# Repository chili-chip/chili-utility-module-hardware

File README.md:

# chili-utility-module

KiCad 10 project for the **chilichip utility module**: a small add-on board for the [chilichip console](https://github.com/chili-chip/vgc-zero-hardware) with a gyroscope/accelerometer, a vibration motor and a real-time clock. Everything sits on one I²C bus, so the module needs only the console's three free GPIOs. The RTC is backed by the console's LiPo through its VSYS rail.

Status: **v2.0.0, schematic and PCB done.** The board is routed, DRC is clean (0 violations, 0 unconnected, matches the schematic), and ERC is clean.

v2.0.0 shrinks the board from 30 × 32 mm to 16.4 × 14.8 mm so it fits on the back of the console (with the RP2350-Plus and its LiPo) between the MCU, the battery and a display mounting hole:
- the CR1220 coin cell is gone: the RTC's backup input comes from the console's VSYS on a sixth castellation (VBAT);
- the 10 mm coin motor with wire leads is replaced by a reflow-solderable 4.3 mm SMD ERM (Vybronics VZ43FC1B5640007L).

| Top | Bottom |
|:---:|:---:|
|  |  |

## Parts

| Ref | Function | Part | LCSC |
|-----|----------|------|------|
| U1 | Gyro + accelerometer | **ST LSM6DS3TR-C**, 6-axis IMU, LGA-14 2.5 × 3 mm | [C967633](https://www.lcsc.com/product-detail/C967633.html) |
| U2 | Real-time clock | **Micro Crystal RV-3028-C7**, crystal built in, 45 nA, SON-8 1.5 × 3.2 mm | [C3019759](https://www.lcsc.com/product-detail/C3019759.html) |
| U3 | Haptic driver | **TI DRV2605L**, I²C ERM/LRA driver with 123 built-in effects, VSSOP-10 | [C527464](https://www.lcsc.com/product-detail/C527464.html) |
| M1 | Vibration motor | **Vybronics VZ43FC1B5640007L**, SMD cylindrical ERM, 4.3 × 4.5 × 12 mm, 3 V, 77 mA typ, reflow-solderable | not on LCSC: [Digi-Key 12323649](https://www.digikey.com/en/products/detail/vybronics-inc/VZ43FC1B5640007L/12323649) |
| C1–C4, C6 | Decoupling | 100 nF 0402, Samsung CL05B104KO5NNNC | C1525 |
| C5, C7 | Driver VDD / REG | 1 µF 0402, Samsung CL05A105KA5NQNC | C52923 |
| R1, R2 | I²C pull-ups | 4.7 kΩ 0402, UNI-ROYAL 0402WGF4701TCE | C25900 |
| R3, R4 | INT pull-up, EVI tie-down | 10 kΩ 0402, UNI-ROYAL 0402WGF1002TCE | C25744 |

Why these parts:
- **LSM6DS3TR-C:** active ST part at about $0.60–0.90, with mature drivers (ST's platform-independent C driver, Adafruit, NuttX).
- **RV-3028-C7:** no external crystal or load capacitors, ±1 ppm, and an automatic switchover to the backup supply (rated 1.1–5.5 V, so the console's VSYS at 3.4–4.95 V can feed it directly; about 115 nA in backup).
- **DRV2605L:** plays haptic effects over I²C, so the motor needs no PWM pin or MOSFET. That matters because the console has no GPIO left for one.

Alternatives considered:
- **QST QMI8658A** IMU: fewer drivers and no KiCad symbol.
- **NXP PCF85063A** RTC: needs an external crystal and draws about 5× more current.
- **MOSFET + flyback diode** for the motor: needs a spare PWM GPIO.
- **CR1220 coin cell** (v1): takes a 20 × 13 mm holder. The console's LiPo holds the RTC for years at 115 nA, as long as the console's off state cuts everything else.

## Connector J1 (to the console)

| Pin | Signal | Console | Notes |
|-----|--------|---------|-------|
| 1 | 3V3 | RP2350-Plus 3V3 | |
| 2 | SDA | GP0 (I2C0 SDA) | 4.7 kΩ pull-up R1 on the module |
| 3 | SCL | GP1 (I2C0 SCL) | 4.7 kΩ pull-up R2 on the module |
| 4 | INT | GP2 | open-drain, shared by IMU INT1 and RTC ~INT; 10 kΩ pull-up R3 |
| 5 | GND | GND | |
| 6 | VBAT | VSYS (pin 39) | RTC backup supply: always on while the console's LiPo is fitted, 3.4–4.95 V. 100 nF C4 at the RTC |

I²C addresses: IMU **0x6A** (SA0 to GND), RTC **0x52**, haptic driver **0x5A**.

GP0/GP1 are also the RP2350's default UART0 pins, so with this module fitted, use USB serial for debug output.

## Firmware setup the hardware relies on

- **IMU:** set INT1 to open-drain (`CTRL3_C` bit `PP_OD = 1`) before enabling any interrupt, because it shares the INT line with the RTC.
- **RTC:**
  - Enable backup switchover in level-switching mode (`BSM = 11` in register 37h) and store it to EEPROM. Switchover is disabled when the chip ships.
  - Leave the trickle charger off (`TCE = 0`, the default): VBACKUP is fed from the console's VSYS, never charged from VDD.
  - CLKOUT outputs 32.768 kHz by default; turn it off to save current.
- **Haptic driver:** select ERM mode and the ERM effect library, then run auto-calibration once for the motor (rated 3.0 V, 2.5–3.4 V operating). The motor's leads are swapped (OUT+ to its − pad) to keep the traces apart; an ERM vibrates the same in either direction. EN is tied high, so put the driver in standby through the `MODE` register when idle.

## ERC

ERC is clean. The project's `LSM6DS3TR-C` symbol has four pin types adjusted from KiCad's original, all matching how this design uses them:
- INT1/INT2 are open-collector, because firmware always sets them to open-drain so they can share the INT line with the RTC.
- SDO/SA0 and SDx are passive, because they're tied to GND: SA0 as an address strap, SDx as the unused auxiliary I²C master.

## Still to check

- **IMU SDx/SCx tie-off:** I tied them to GND, which is what secondary pin summaries say ("connect to VDDIO or GND" when unused). Check this against ST's LSM6DS3TR-C datasheet (DocID030071) pin table.
- **Power budget:** the motor draws about 77 mA (100 mA max) at 3 V while running, from the RP2350-Plus's 3.3 V output.
- **Motor sourcing:** the VZ43FC1B isn't stocked by LCSC. For JLCPCB assembly, use their global sourcing (Digi-Key) or consign the parts, or pick an LCSC-stocked SMD ERM with the same land pattern.

## Footprints

| Ref | Footprint | Source |
|-----|-----------|--------|
| J1 | `Castellated_1x06_P2.54mm` | Same castellated pads as the audio and buttons modules: 1.0 mm drill, 2.4 × 1.6 mm, on the board edge |
| M1 | `Motor_ERM_SMD_Vybronics_VZ43FC1B` | Vybronics datasheet land pattern: frame pad 3.4 × 9 mm (no net), terminals 1.3 × 1.4 mm. The counterweight end overhangs the frame pad and must stay clear |
| U2 | `MicroCrystal_C7_SON-8_1.5x3.2mm_P0.9mm` | Copy of KiCad's footprint, because KiCad 10 doesn't ship the 3D model it references |
| U1, U3, passives | KiCad standard library | |

**3D models:** U1, U3 and the passives use KiCad's library models. U2 uses LCSC's STEP model (from their EasyEDA library) and M1 Vybronics' STEP model, stored in `3d-models/`.

## PCB

- **Board:** 16.4 × 14.8 mm, 2 layers, all parts on the top side, 4.3 mm tall at the motor. The bottom sits flat on the back of the console once J1's castellations are soldered; the console's `UtilityModule` footprint has the matching lands.
- **Placement:**
  - J1 on the left edge, with the I²C/INT pull-ups in a column next to their castellations.
  - RTC at the top (next to VBAT), IMU below it, haptic driver at the bottom, each with its capacitors to its right.
  - Motor along the right edge, terminals at the bottom next to the driver's outputs.
- **Ground:** GND pour on both layers. SMD pads connect solid, through-hole pads through thermal spokes, and J1's GND castellation solid.
- **Routing:** autorouted with Freerouting, GND included as tracks, with keep-outs along the edges and between the castellations for the 0.5 mm copper-to-edge clearance. Tracks are 0.15 mm, necked to 0.125 mm where they pass fine-pitch pads, with 0.15 mm clearance; JLCPCB's minimum is 0.127 mm (DRC minimum set to 0.12 mm).
- **Silkscreen:** the version on top; J1 pin labels (VB, G, IN, SC, SD, 3V) and the module name on the bottom, since the top has no room. Reference designators are on the fab layer.

## Ordering from JLCPCB

Every tagged release has `chili-utility-module-<version>-gerbers.zip`, `-bom.csv` and `-cpl.csv` attached. Run `scripts/export-jlcpcb.sh` to build them locally into `production/`.

1. Upload the gerber zip on [jlcpcb.com](https://jlcpcb.com/) and select **2 layers, 1.6 mm, Castellated Holes: Yes**.
2. Turn on **PCB Assembly** (top side) and upload the BOM and CPL.
3. In the placement preview, check pin 1 of U1–U3 and the motor's orientation (terminals at the bottom, next to U3).
4. The motor (M1) has no LCSC part number: source it through JLCPCB global sourcing or consign it. Don't wash the board after assembly: the motor must not get flux washes or conformal coating.

CI runs ERC, DRC and the export on every push and pull request. A `v*` tag publishes a release with the files attached.

## Files

| Path | Contents |
|------|----------|
| `chili-utility-module.kicad_sch` | Schematic |
| `chili-utility-module.kicad_sym`, `sym-lib-table` | Project symbols: LSM6DS3TR-C, RV-3028-C7, DRV2605L, Motor_ERM. Copied from KiCad 10's library, with manufacturer, part number and LCSC fields added |
| `chili-utility-module.pretty/`, `fp-lib-table` | Project footprints: J1 castellated 1×06, M1 Vybronics SMD motor, U2 SON-8 |
| `3d-models/` | STEP models for M1 and U2 |
| `chili-utility-module.kicad_pcb` | PCB |
| `scripts/export-jlcpcb.sh` | Builds the JLCPCB gerber zip, BOM and CPL |
| `scripts/render-images.sh` | Regenerates the renders in `docs/images/` |
| `.github/workflows/main.yml` | CI and release workflow |

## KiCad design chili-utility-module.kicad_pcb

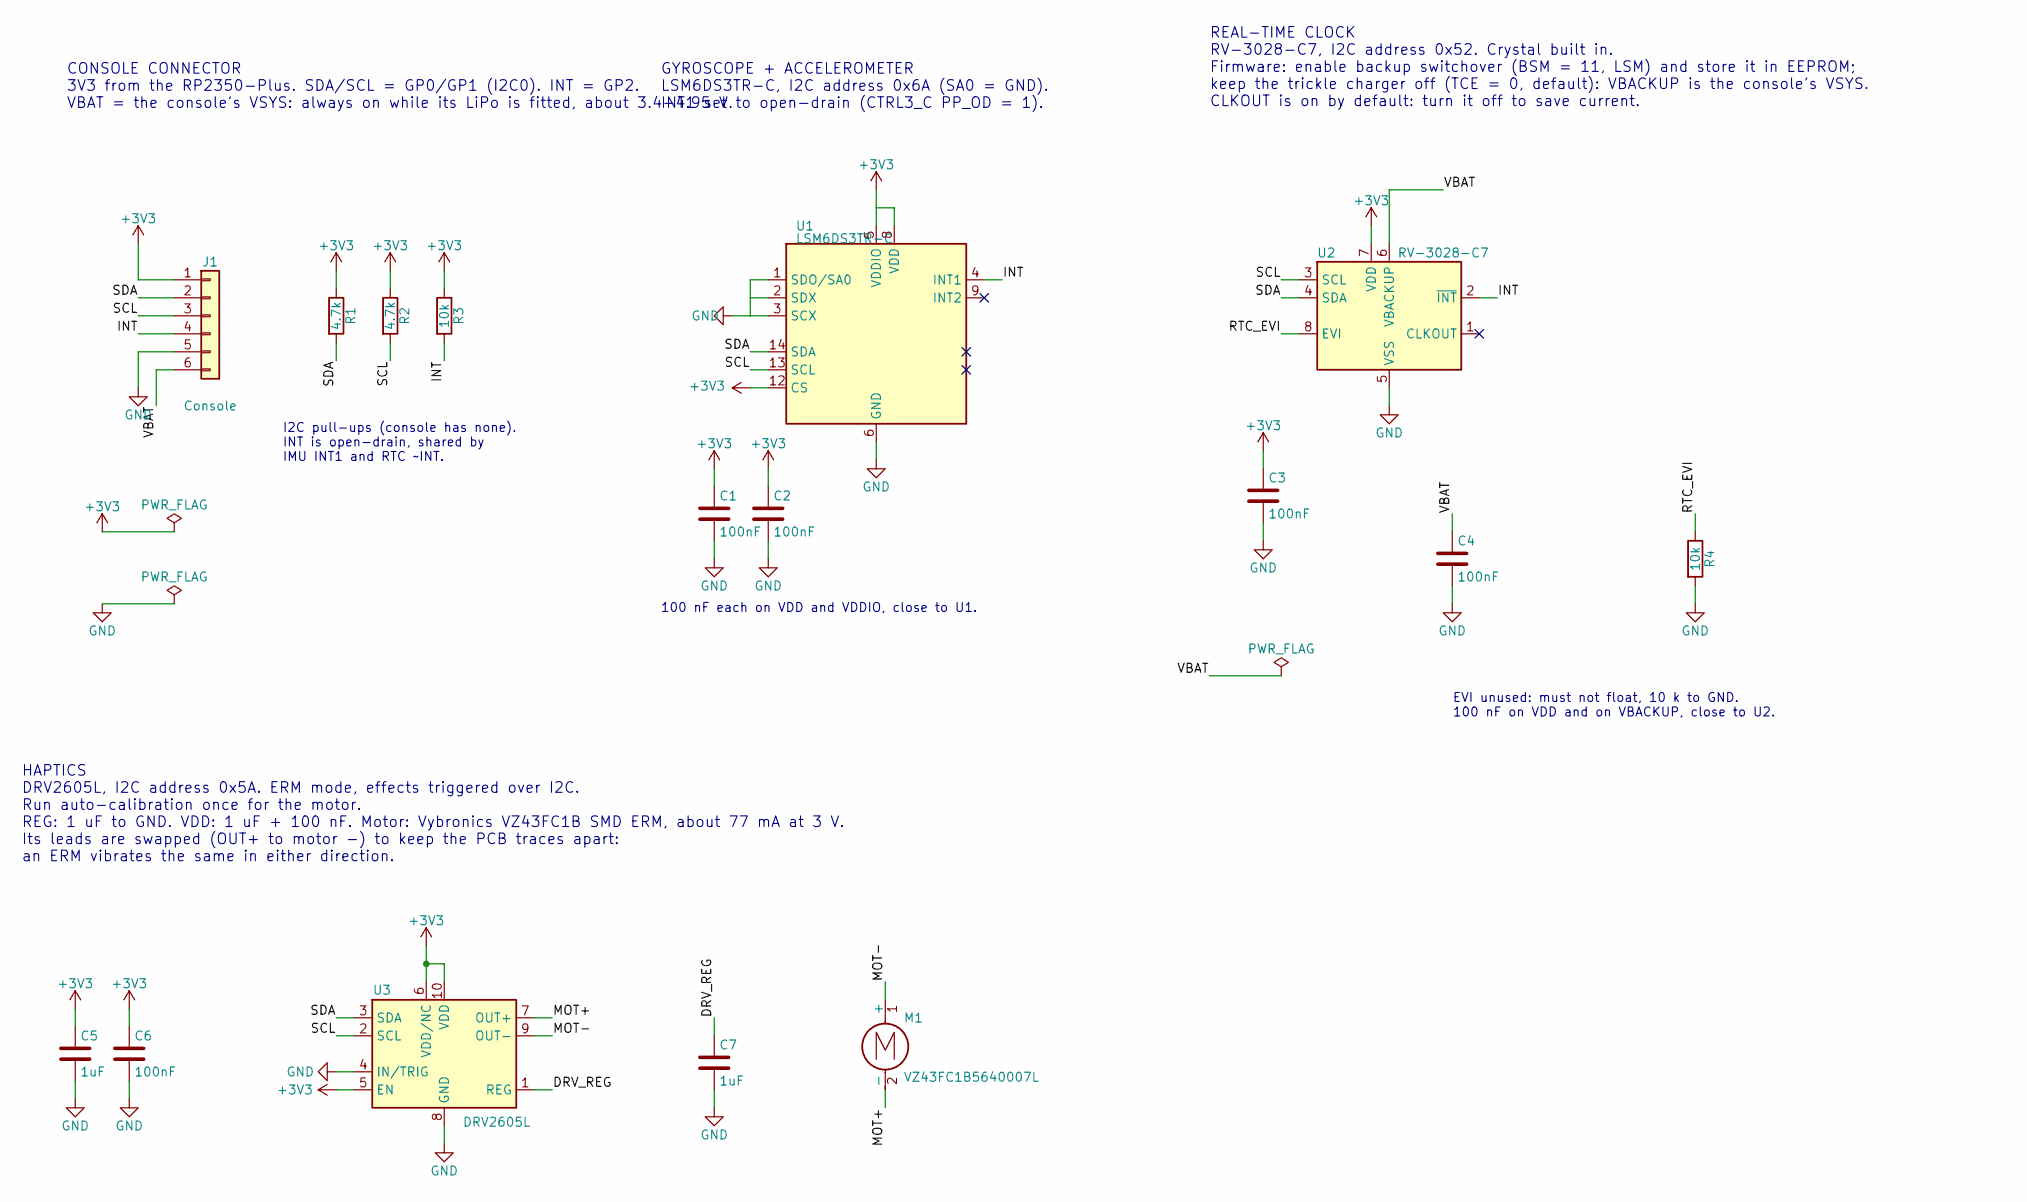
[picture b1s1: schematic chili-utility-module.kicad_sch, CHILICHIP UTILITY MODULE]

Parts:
C1, C2, C3, C4, C6: 100nF; C_0402_1005Metric; MPN CL05B104KO5NNNC; LCSC C1525
C5, C7: 1uF; C_0402_1005Metric; MPN CL05A105KA5NQNC; LCSC C52923
J1: Console; Castellated_1x06_P2.54mm
M1: VZ43FC1B5640007L; Motor_ERM_SMD_Vybronics_VZ43FC1B; MPN VZ43FC1B5640007L
R1, R2: 4.7k; R_0402_1005Metric; MPN 0402WGF4701TCE; LCSC C25900
R3, R4: 10k; R_0402_1005Metric; MPN 0402WGF1002TCE; LCSC C25744
U1: LSM6DS3TR-C; LGA-14_3x2.5mm_P0.5mm_LayoutBorder3x4y; MPN LSM6DS3TR-C; LCSC C967633
U2: RV-3028-C7; MicroCrystal_C7_SON-8_1.5x3.2mm_P0.9mm; MPN RV-3028-C7-32.768kHz-1ppm-TA-QC; LCSC C3019759
U3: DRV2605L; TSSOP-10_3x3mm_P0.5mm; MPN DRV2605LDGSR; LCSC C527464

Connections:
+3V3: C1.1, C2.1, C3.1, C5.1, C6.1, J1.1, R1.1, R2.1, R3.1, U1.5 (VDDIO), U1.8 (VDD), U1.12 (CS), U2.7 (VDD), U3.5 (EN), U3.6 (VDD/NC), U3.10 (VDD)
/DRV_REG: C7.1, U3.1 (REG)
/INT: J1.4, R3.2, U1.4 (INT1), U2.2 (~INT)
/MOT+: M1.2 (-), U3.7 (OUT+)
/MOT-: M1.1 (+), U3.9 (OUT-)
/RTC_EVI: R4.1, U2.8 (EVI)
/SCL: J1.3, R2.2, U1.13 (SCL), U2.3 (SCL), U3.2 (SCL)
/SDA: J1.2, R1.2, U1.14 (SDA), U2.4 (SDA), U3.3 (SDA)
/VBAT: C4.1, J1.6, U2.6 (VBACKUP)
GND: C1.2, C2.2, C3.2, C4.2, C5.2, C6.2, C7.2, J1.5, R4.2, U1.1 (SDO/SA0), U1.2 (SDX), U1.3 (SCX), U1.6 (GND), U1.7 (GND), U2.5 (VSS), U3.4 (IN/TRIG), U3.8 (GND)

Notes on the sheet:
100 nF each on VDD and VDDIO, close to U1.
CONSOLE CONNECTOR 3V3 from the RP2350-Plus. SDA/SCL = GP0/GP1 (I2C0). INT = GP2. VBAT = the console's VSYS: always on while its LiPo is fitted, about 3.4-4.95 V.
I2C pull-ups (console has none). INT is open-drain, shared by IMU INT1 and RTC ~INT.
HAPTICS DRV2605L, I2C address 0x5A. ERM mode, effects triggered over I2C. Run auto-calibration once for the motor. REG: 1 uF to GND. VDD: 1 uF + 100 nF. Motor: Vybronics VZ43FC1B SMD ERM, about 77 mA at 3 V. Its leads are swapped (OUT+ to motor -) to keep the PCB traces apart: an ERM vibrates the s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
GYROSCOPE + ACCELEROMETER LSM6DS3TR-C, I2C address 0x6A (SA0 = GND). INT1 set to open-drain (CTRL3_C PP_OD = 1).
REAL-TIME CLOCK RV-3028-C7, I2C address 0x52. Crystal built in. Firmware: enable backup switchover (BSM = 11, LSM) and store it in EEPROM; keep the trickle charger off (TCE = 0, default): VBACKUP is the console's VSYS. CLKOUT is on by default: turn it off to save current.
EVI unused: must not float, 10 k to GND. 100 nF on VDD and on VBACKUP, close to U2.

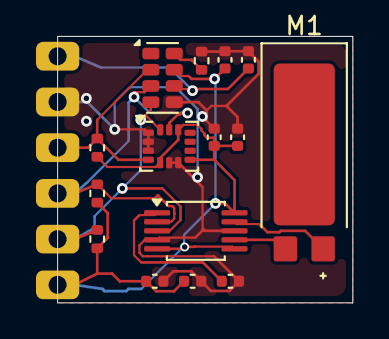
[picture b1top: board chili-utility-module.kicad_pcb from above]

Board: 2 copper layers, 16.4 x 14.8 mm, 16 parts (0 on the bottom side), 10 nets.
